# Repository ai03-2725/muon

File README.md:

# muon
Minimal USB-C to JST-SH daughterboard PCBs

**Currently in development; not finalized or tested.**

## Variants

### Variant A (latest revision A2)
Narrow and wide variant

### Variant B (latest revision B2)
Symmmetrical and rectangular variant

## Features

- Physically compact
  - 31.50 x 10.00 mm for Variant A
  - 20.00 x 13.50 mm for Variant B
  - Balanced minimizing of dimensions with a focus on ease of implementation on the case-side
- Physically robust
  - 2x M2.5 screws for a balance between robustness, ease of manufacturing, user-friendliness, and physical compactness
  - 1.6mm PCB to counter cable torque and resist over-tensioned screw-in by users
- Minimal, practical implementation
  - Single-sided for easy assembly - whether at a factory or reflowing at home
  - Two-layer for affordable manufacturing
  - 3D printable solder paste stencil file included (0.2mm nozzle and line width, 0.08mm layer height)
  - Asymmetrical design with protruding USB port prevents accidental reverse installation by users
- Optimized for ease of case design
  - Straightforward, rational dimensions
  - Large USB connector overhang for case-side flexibility and robustness
  - Can be mounted component-side-up or component-side-down for prioritizing ease of servicing or physical compactness respectively  
  - 3D models and example case-side implementation provided (see the References folders in the Var-A/Var-B directories)
  - Designed with aesthetics in mind to avoid detracting from case visuals  
  - Example implementations can be CNC-machined with 2mm inner radius
- Proven circuitry and implementation based on the [Unified Daughterboard series](https://unified-daughterboard.github.io/#/)
  - ESD/overcurrent/overvoltage protection, single-path grounding of case via mounting screws
  - JST-SH connector with identical pinout to the Unified Daughterboard

## Dimensions
Mounting screws are M2.5.  
Only use flat screws - countersunk screws apply focused angled pressure on the screw holes and risk shattering the board apart.  
  
Recommended max diameter for screw heads/standoffs/mounting points contacting the board is 5.00mm centered on the mounting holes.  
Absolute max diameter is 6.0mm; ESD handling capabilities may be reduced when exceeding 5.00mm.  

### Variant A
Ends are roughly 5.00mm radius (slightly inset from a tangent arc for visual reasons).

### Variant B
Corners are roughly 1.85mm radius (slightly inset from a tangent arc for visual reasons).

## Pinout

Pinout is identical to the Unified Daughterboard series.  
Only use a one-to-one cable (the same type used on the Unified Daughterboard JST-type boards; pin 1 of one end maps to pin 1 of the other end).

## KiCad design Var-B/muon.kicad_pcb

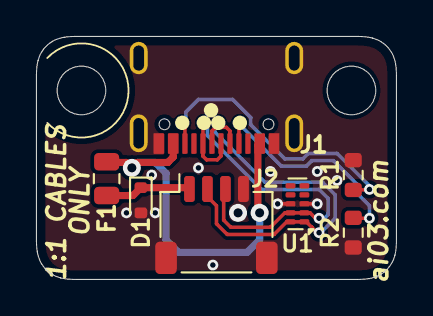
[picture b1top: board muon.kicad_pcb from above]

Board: 2 copper layers, 20.0 x 13.5 mm, 9 parts (0 on the bottom side), 7 nets.

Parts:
D1: ESD5Z5V0; D_SOD-523
F1: SMD0805-100-16; Fuse_0805_2012Metric
J1: HRO_TYPE-C-31-M-12; HRO-TYPE-C-31-M-12-Assembly-Minimal
J2: SM04B-SRSS-TB; JST_SH_SM04B-SRSS-TB_1x04-1MP_P1.00mm_Horizontal_SmallerPads
MH1, MH2: Pad-M2.5; MountingHole-M2.5-Simple
R1, R2: 5.1k; R_0603_1608Metric
U1: TPD4E05U06DQA; USON-10_2.5x1.0mm_P0.5mm

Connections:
+5V: D1.1 (K), F1.2, J2.1
CC1: J1.A5 (CC1), R2.1
CC2: J1.B5 (CC2), R1.1
D+: J1.A6 (D+), J1.B6 (D+), J2.3, U1.2 (D1-)
D-: J1.A7 (D-), J1.B7 (D-), J2.2, U1.1 (D1+)
GND: D1.2 (A), J1.A1 (GND), J1.A12 (GND), J1.S1 (SHIELD), J2.4, J2.MP (MountPin), R1.2, R2.2, U1.3 (GND), U1.8 (GND)
VBUS: F1.1, J1.A4 (VBUS), J1.A9 (VBUS)

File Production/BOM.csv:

Reference,Qty,Value,Footprint,JLC Part Number
D1,1,ESD5Z5V0,Diode_SMD:D_SOD-523,C727161
F1,1,SMD0805-100-16,Fuse:Fuse_0805_2012Metric,C968441
J1,1,HRO_TYPE-C-31-M-12,locallib:HRO-TYPE-C-31-M-12-Assembly,C165948
J2,1,SM04B-SRSS-TB,Connector_JST:JST_SH_SM04B-SRSS-TB_1x04-1MP_P1.00mm_Horizontal,C160404
"R1,R2",2,5.1k,Resistor_SMD:R_0603_1608Metric,C25905
U1,1,TPD4E05U06DQA,Package_SON:USON-10_2.5x1.0mm_P0.5mm,C2836386

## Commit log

2025-12-26 Add screenshots
2025-12-26 Add dimensions image
2025-12-28 Update to A2 revision
2025-12-28 Update pinout and readme
2025-12-28 Add reference implementation
2025-12-28 Make B variant
2025-12-28 Update A2 gerbers with new silkscreen
2025-12-28 Fix header order
2025-12-28 Add note regarding outer radii
2025-12-28 Add reference implementation for B
2025-12-28 Update A gerbers with fixed USB-C footprint
2026-01-05 Update B variant to B2
2026-01-05 Adjust silkscreen; update gerber
2026-01-05 Adjust silkscreen
2026-01-05 Add reference implementation for B2
2026-01-06 Remove redundant silkscreen
2026-02-05 Update stencils
